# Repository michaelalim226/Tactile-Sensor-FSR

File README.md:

# 🖐️ Tactile Sensor with Force Sensitive Resistor (FSR)

A **low-cost tactile sensing system** using **Force Sensitive Resistors (FSRs)** as input, designed to measure applied pressure and convert it into a digital signal.  
This project provides **hardware schematics, PCB layouts, and Arduino firmware** for implementing a tactile sensor interface.

---

## 📌 Project Overview

This project explores the design and implementation of a **tactile sensor module** based on FSR input circuits.  
Two amplifier configurations are compared:

- **LM358-based amplifier**  
- **MCP602-based amplifier**

Both designs aim to provide **stable, noise-resistant** readings from the FSR sensor, which are then monitored via Arduino.

---

## ⚡ Features
- Arduino-based FSR monitoring firmware (`FSR_Monitor.ino`)  
- Hardware schematics (`.sch`) and PCB layouts (`.brd`)  
- Support for **LM358** and **MCP602** op-amp circuits  
- Visual reference: schematic diagrams and PCB board previews  

---

## 🛠️ Hardware Design

📂 **`/hardware` folder includes:**
- `FSR Input LM358.sch` & `FSR Input LM358.brd`  
- `FSR Input MCP602.sch` & `FSR Input MCP602.brd`  
- `eagle.epf` (Eagle project file)  

📂 **`/image` folder includes:**
- `Schematic_lm358.png`  
- `Schematic_mcp602.png`  
- `board_lm358.png`  
- `board_mcp602.png`  

Example Schematic (LM358):  

Example PCB Layout (MCP602):  

---

## 💻 Arduino Firmware

The `code/FSR_Monitor.ino` provides real-time monitoring of sensor values.

```cpp
// Example snippet from FSR_Monitor.ino
int fsrPin = A0;
int fsrReading;

void setup() {
  Serial.begin(9600);
}

void loop() {
  fsrReading = analogRead(fsrPin);
  Serial.println(fsrReading);
  delay(100);
}
```

👉 Full code available in [`code/FSR_Monitor.ino`](./code/FSR_Monitor.ino)

---

## 🚀 Applications

* Robotic tactile sensing  
* Grip force measurement  
* Human-computer interaction (HCI)  
* Pressure-sensitive switches  

---

## 🔮 Potential Improvements

* Add calibration curves for force vs resistance  
* Implement multi-FSR array sensing  
* Integrate wireless data transmission (BLE / WiFi)  

---

## 🔬 Op-Amp Comparison: LM358 vs MCP602

| Specification        | **LM358**                          | **MCP602**                                  |
|----------------------|------------------------------------|---------------------------------------------|
| **Op-Amp Type**      | Dual Operational Amplifier         | Dual Operational Amplifier                   |
| **Supply Voltage**   | 3V – 32V (single supply)           | 2.7V – 6V (single supply)                    |
| **Input Offset**     | ±7 mV (typical)                    | ±2 mV (typical)                              |
| **Input Bias Current** | ~20 nA                           | ~1 pA                                        |
| **Bandwidth (GBW)**  | 1 MHz                              | 10 MHz                                       |
| **Slew Rate**        | 0.3 V/µs                           | 7 V/µs                                       |
| **Input Impedance**  | ~2 MΩ                              | >10 TΩ (very high)                           |
| **Output Drive**     | Can drive medium load              | Stronger, suitable for precision sensing     |
| **Advantages**       | Cheap, easy to find                | Low noise, fast, great for ADC/sensors       |
| **Drawbacks**        | Slower, higher noise               | Limited supply voltage (max 6V)              |

---

## 📄 License

This project is licensed under the [MIT License](LICENSE).

---

## 💡 Tips (Brick Section)

- Use **MCP602** if precision and low-noise operation are required.  
- Use **LM358** if cost and flexible supply voltage are the main concerns.  
- Add a **pull-down resistor** for more stable readings.  
- Calibrate the FSR before using it in real-world applications.

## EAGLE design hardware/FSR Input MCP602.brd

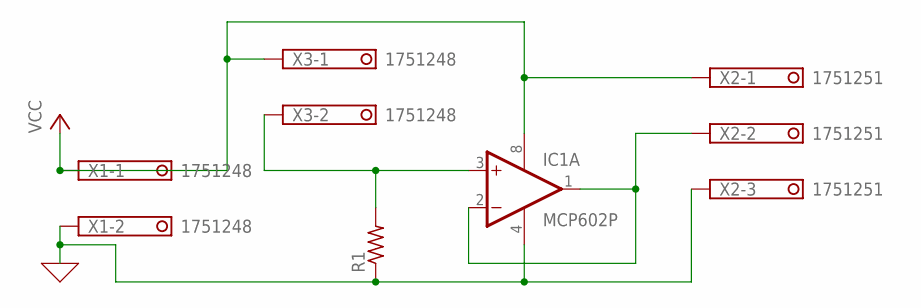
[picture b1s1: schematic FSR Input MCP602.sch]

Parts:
IC1: MCP602P; DIL08
R1: R-US_0204/5; 0204/5
X1, X3: 1751248
X2: 1751251

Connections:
0: IC1.4 (V-), R1.1, X1.2, X2.3
unnamed: IC1.3 (+IN), R1.2, X3.2
unnamed: IC1.1 (OUT), IC1.2 (-IN), X2.2
VCC: IC1.8 (V+), X1.1, X2.1, X3.1

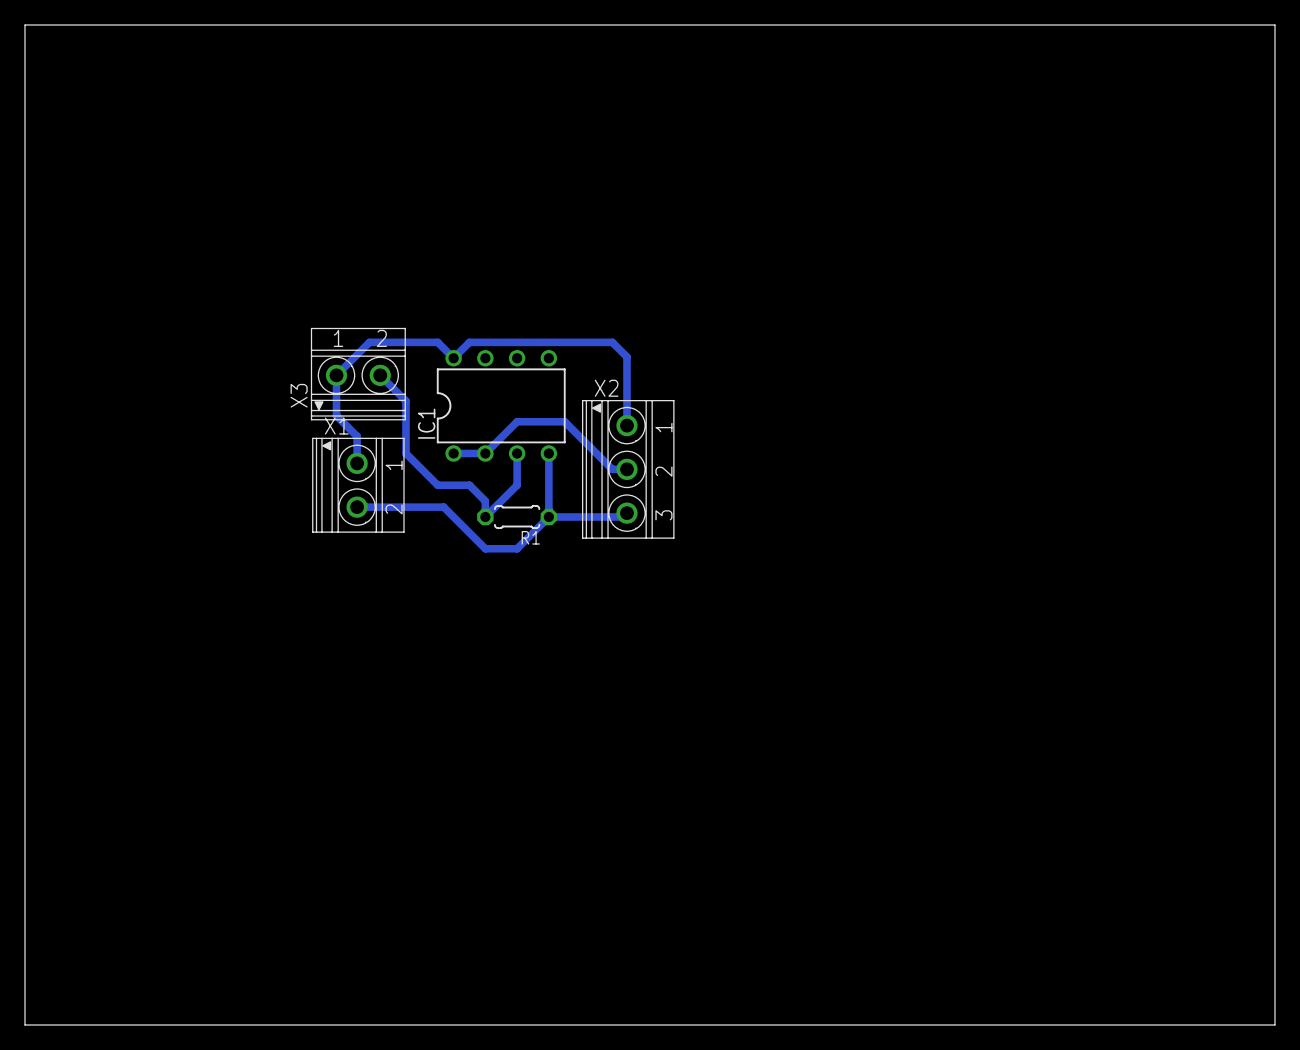
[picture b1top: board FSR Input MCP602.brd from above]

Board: 2 copper layers, 100.0 x 80.0 mm, 5 parts (0 on the bottom side), 4 nets.

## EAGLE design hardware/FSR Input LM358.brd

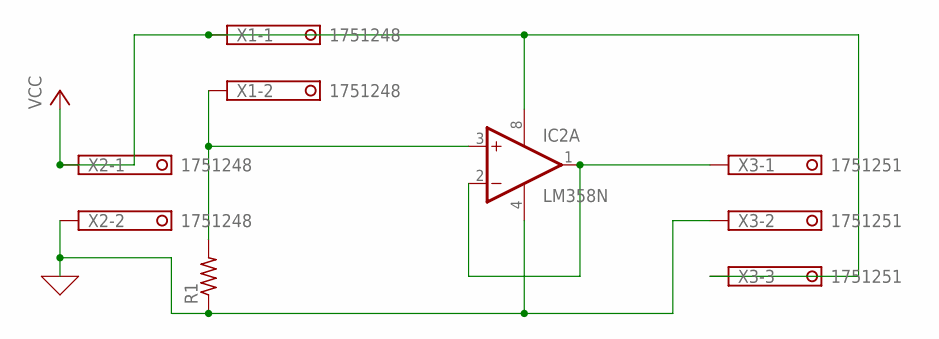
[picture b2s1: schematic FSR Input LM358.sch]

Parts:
IC2: LM358N; DIL08
R1: R-US_0204/5; 0204/5
X1, X2: 1751248
X3: 1751251

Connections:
0: IC2.4 (V-), R1.1, X2.2, X3.2
unnamed: IC2.3 (+IN), R1.2, X1.2
unnamed: IC2.1 (OUT), IC2.2 (-IN), X3.1
VCC: IC2.8 (V+), X1.1, X2.1, X3.3

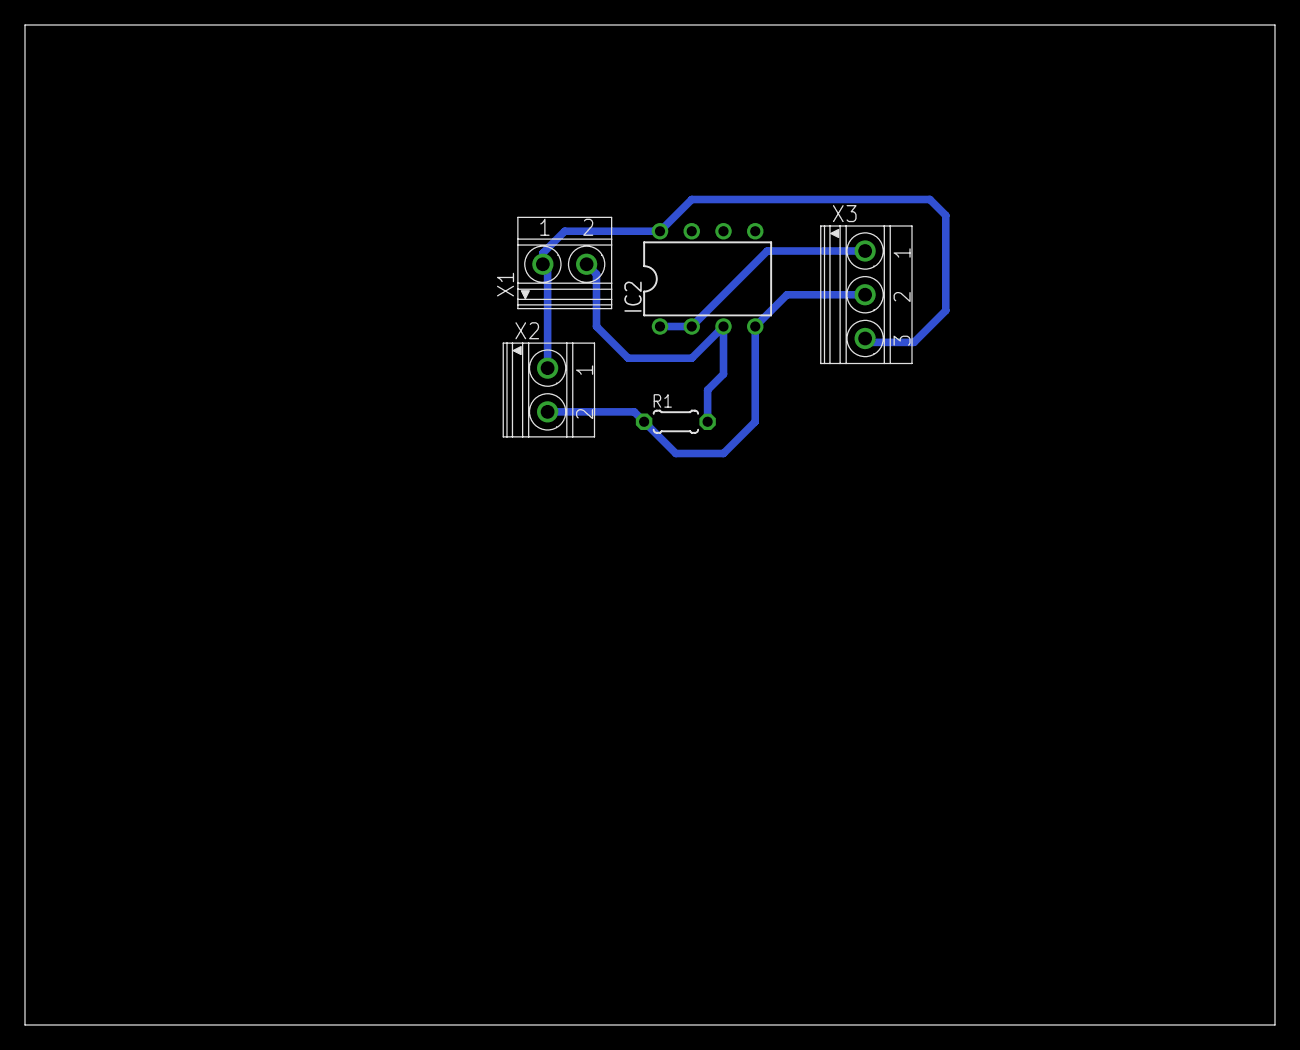
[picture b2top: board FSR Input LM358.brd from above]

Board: 2 copper layers, 100.0 x 80.0 mm, 5 parts (0 on the bottom side), 4 nets.

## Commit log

2025-08-21 README.md
